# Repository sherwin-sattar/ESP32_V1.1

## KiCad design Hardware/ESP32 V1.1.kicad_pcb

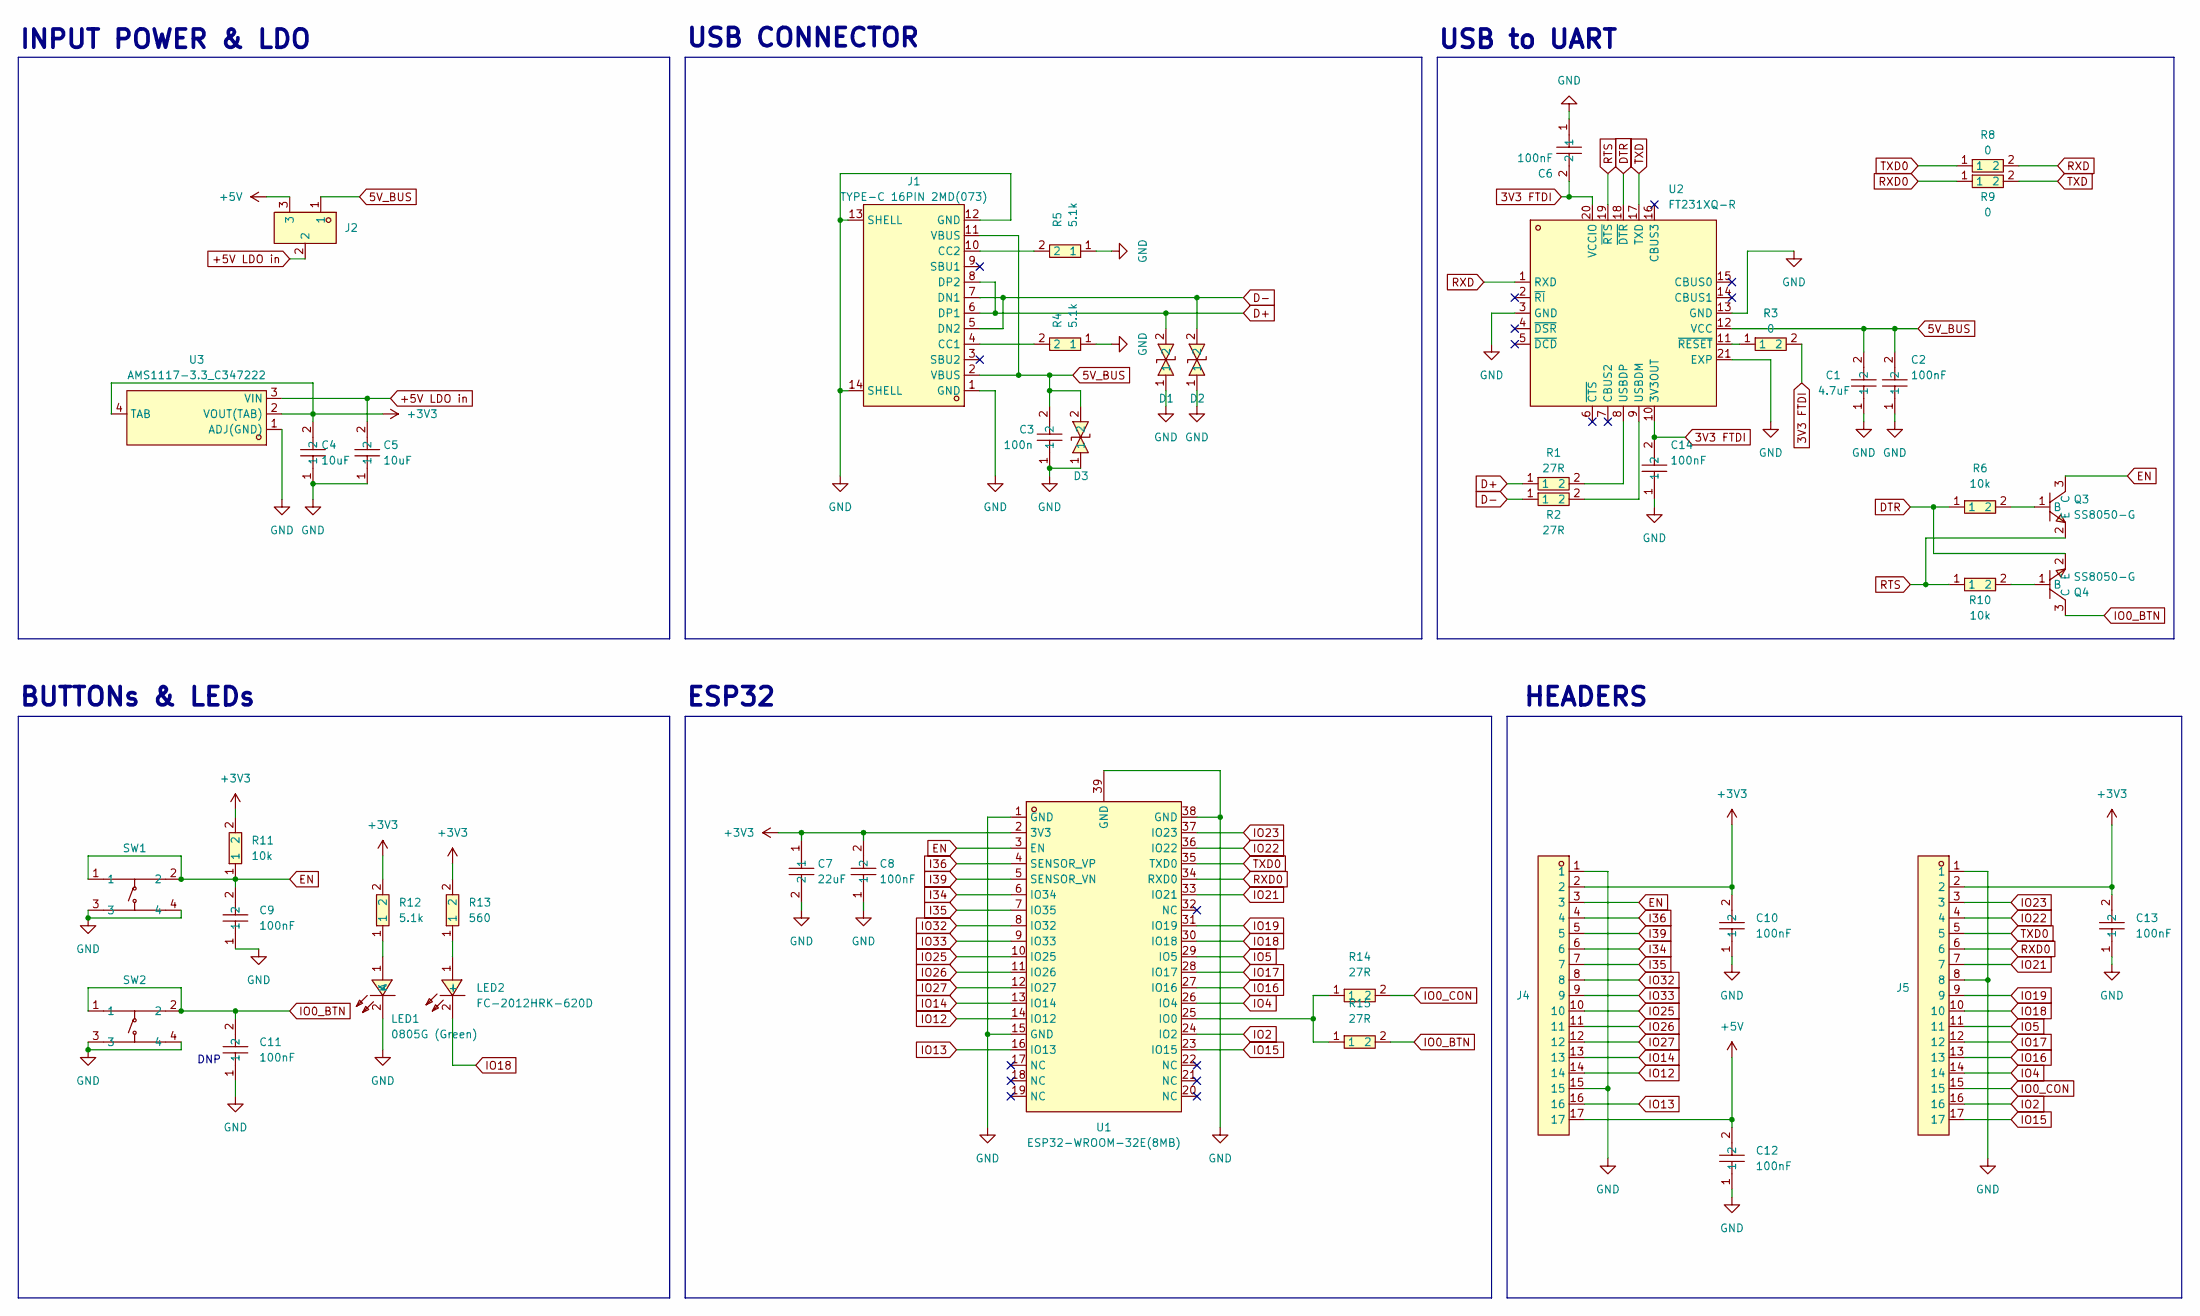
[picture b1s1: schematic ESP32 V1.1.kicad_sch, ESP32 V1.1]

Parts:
C1: 4.7uF; C0402; LCSC Part C368809
C2, C6, C8, C9, C10, C11, C12, C13, C14: 100nF; C0402; LCSC Part C1525
C3: 100n; C0402; LCSC Part C1525
C4, C5: 10uF; C0402; LCSC Part C315248
C7: 22uF; C0805; LCSC Part C602037
D1, D2, D3: SOD-523_L1.2-W0.8-LS1.6-BI; LCSC Part C383211
J1: TYPE-C 16PIN 2MD(073); USB-C-SMD_TYPE-C-6PIN-2MD-073; LCSC Part C2765186
J2: X1311WVS-03J-C40D42R2; HDR-SMD_3P-P1.27-V-M-LS4.2_X1311WVS-03J-C40D42R2; LCSC Part C5243526
J4, J5: X6511WV-17H-C30D60; HDR-TH_17P-P2.54-V-M; LCSC Part C725949
LED1: 0805G (Green); LED0805-R-RD; LCSC Part C2297
LED2: FC-2012HRK-620D; LED0805-R-RD; LCSC Part C84256
Q3, Q4: SS8050-G; SOT-23-3_L2.9-W1.3-P1.90-LS2.4-BR; LCSC Part C164886
R1, R2, R14, R15: 27R; R0402; LCSC Part C138021
R3, R8, R9: 0; R0402; LCSC Part C17168
R4, R5, R12: 5.1k; R0402; LCSC Part C25905
R6, R10, R11: 10k; R0402; LCSC Part C25744
R13: 560; R0402; LCSC Part C25126
SW1, SW2: PTS645SH50SMTR92LFS; KEY-SMD_4P-L6.0-W6.0-P4.50-LS9.0; LCSC Part C221869
U1: ESP32-WROOM-32E(8MB); WIFI-SMD_ESP32-WROOM-32E; LCSC Part C701342
U2: FT231XQ-R; QFN-20_L4.0-W4.0-P0.50-BL-EP2.2; LCSC Part C132159
U3: AMS1117-3.3_C347222; SOT-223-4_L6.5-W3.5-P2.30-LS7.0-BR; LCSC Part C347222

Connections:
3V3 FTDI: C6.2, C14.2, R3.2, U2.10 (3V3OUT), U2.20 (VCCIO)
5V_BUS: C1.2, C2.2, C3.2, D3.2, J1.2 (VBUS), J1.11 (VBUS), J2.1, U2.12 (VCC)
+3V3: C4.2, C7.1, C8.2, C10.2, C13.2, J4.2, J5.2, R11.2, R12.2, R13.2, U1.2 (3V3), U3.2 (VOUT(TAB)), U3.4 (TAB)
+5V: C12.2, J2.3, J4.17
+5V LDO in: C5.2, J2.2, U3.3 (VIN)
D+: D1.2, J1.6 (DP1), J1.8 (DP2), R1.1
D-: D2.2, J1.5 (DN2), J1.7 (DN1), R2.1
DTR: Q4.2 (E), R6.1, U2.18 (~DTR)
EN: C9.2, J4.3, Q3.3 (C), R11.1, SW1.1, SW1.2, U1.3 (EN)
GND: C1.1, C2.1, C3.1, C4.1, C5.1, C6.1, C7.2, C8.1, C9.1, C10.1, C11.1, C12.1, C13.1, C14.1, D1.1, D2.1, D3.1, J1.1 (GND), J1.12 (GND), J1.13 (SHELL), J1.14 (SHELL), J4.1, J4.15, J5.1, J5.8, LED1.2 (K), R4.1, R5.1, SW1.3, SW1.4, SW2.3, SW2.4, U1.1 (GND), U1.15 (GND), U1.38 (GND), U1.39 (GND), U2.3 (GND), U2.13 (GND), U2.21 (EXP), U3.1 (ADJ(GND))
I34: J4.6, U1.6 (IO34)
I35: J4.7, U1.7 (IO35)
I36: J4.4, U1.4 (SENSOR_VP)
I39: J4.5, U1.5 (SENSOR_VN)
IO0_BTN: C11.2, Q4.3 (C), R15.2, SW2.1, SW2.2
IO0_CON: J5.15, R14.2
IO2: J5.16, U1.24 (IO2)
IO4: J5.14, U1.26 (IO4)
IO5: J5.11, U1.29 (IO5)
IO12: J4.14, U1.14 (IO12)
IO13: J4.16, U1.16 (IO13)
IO14: J4.13, U1.13 (IO14)
IO15: J5.17, U1.23 (IO15)
IO16: J5.13, U1.27 (IO16)
IO17: J5.12, U1.28 (IO17)
IO18: J5.10, LED2.2 (-), U1.30 (IO18)
IO19: J5.9, U1.31 (IO19)
IO21: J5.7, U1.33 (IO21)
IO22: J5.4, U1.36 (IO22)
IO23: J5.3, U1.37 (IO23)
IO25: J4.10, U1.10 (IO25)
IO26: J4.11, U1.11 (IO26)
IO27: J4.12, U1.12 (IO27)
IO32: J4.8, U1.8 (IO32)
IO33: J4.9, U1.9 (IO33)
unnamed: J1.4 (CC1), R4.2
unnamed: J1.10 (CC2), R5.2
unnamed: LED1.1 (A), R12.1
unnamed: LED2.1 (+), R13.1
unnamed: Q3.1 (B), R6.2
unnamed: Q4.1 (B), R10.2
unnamed: R14.1, R15.1, U1.25 (IO0)
unnamed: R2.2, U2.9 (USBDM)
unnamed: R1.2, U2.8 (USBDP)
unnamed: R3.1, U2.11 (~RESET)
RTS: Q3.2 (E), R10.1, U2.19 (~RTS)
RXD: R8.2, U2.1 (RXD)
RXD0: J5.6, R9.1, U1.34 (RXD0)
TXD: R9.2, U2.17 (TXD)
TXD0: J5.5, R8.1, U1.35 (TXD0)

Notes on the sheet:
USB CONNECTOR
BUTTONs & LEDs
ESP32
INPUT POWER & LDO
HEADERS
USB to UART
DNP

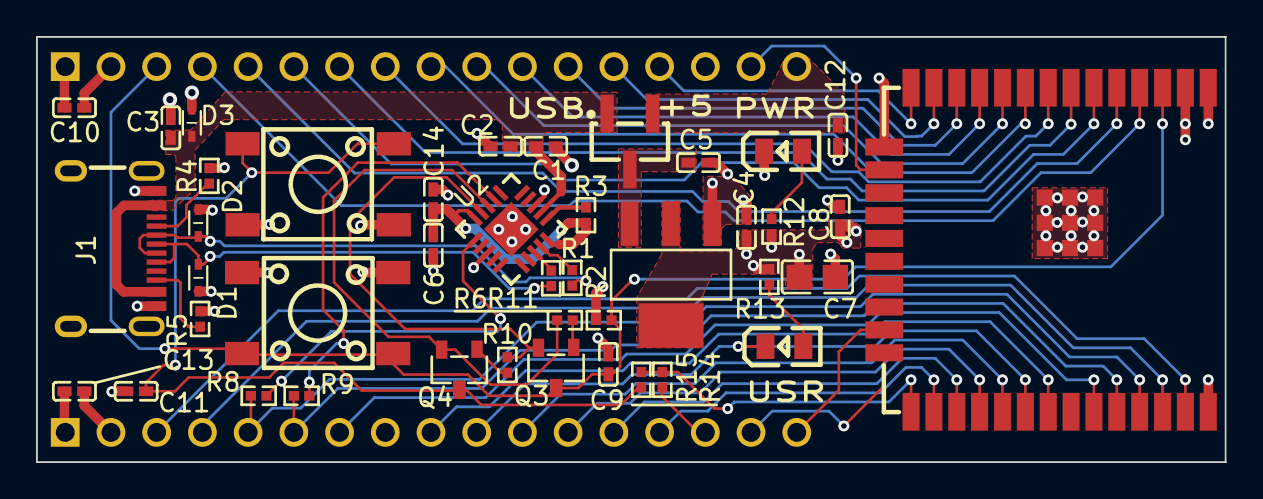
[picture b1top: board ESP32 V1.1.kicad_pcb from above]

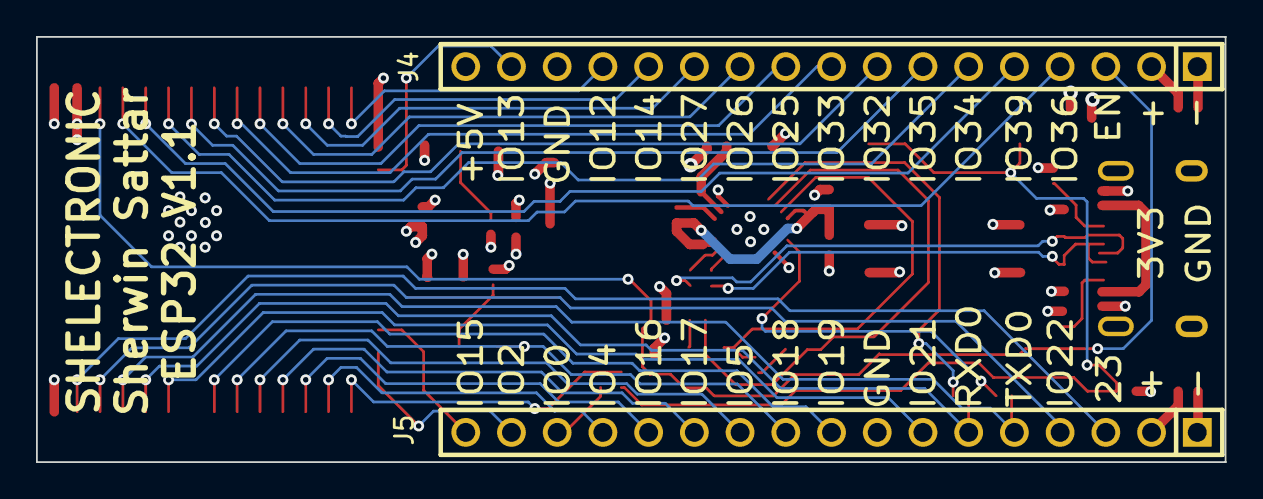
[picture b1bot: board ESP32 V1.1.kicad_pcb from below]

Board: 4 copper layers, 66.0 x 23.6 mm, 44 parts (2 on the bottom side), 50 nets.
